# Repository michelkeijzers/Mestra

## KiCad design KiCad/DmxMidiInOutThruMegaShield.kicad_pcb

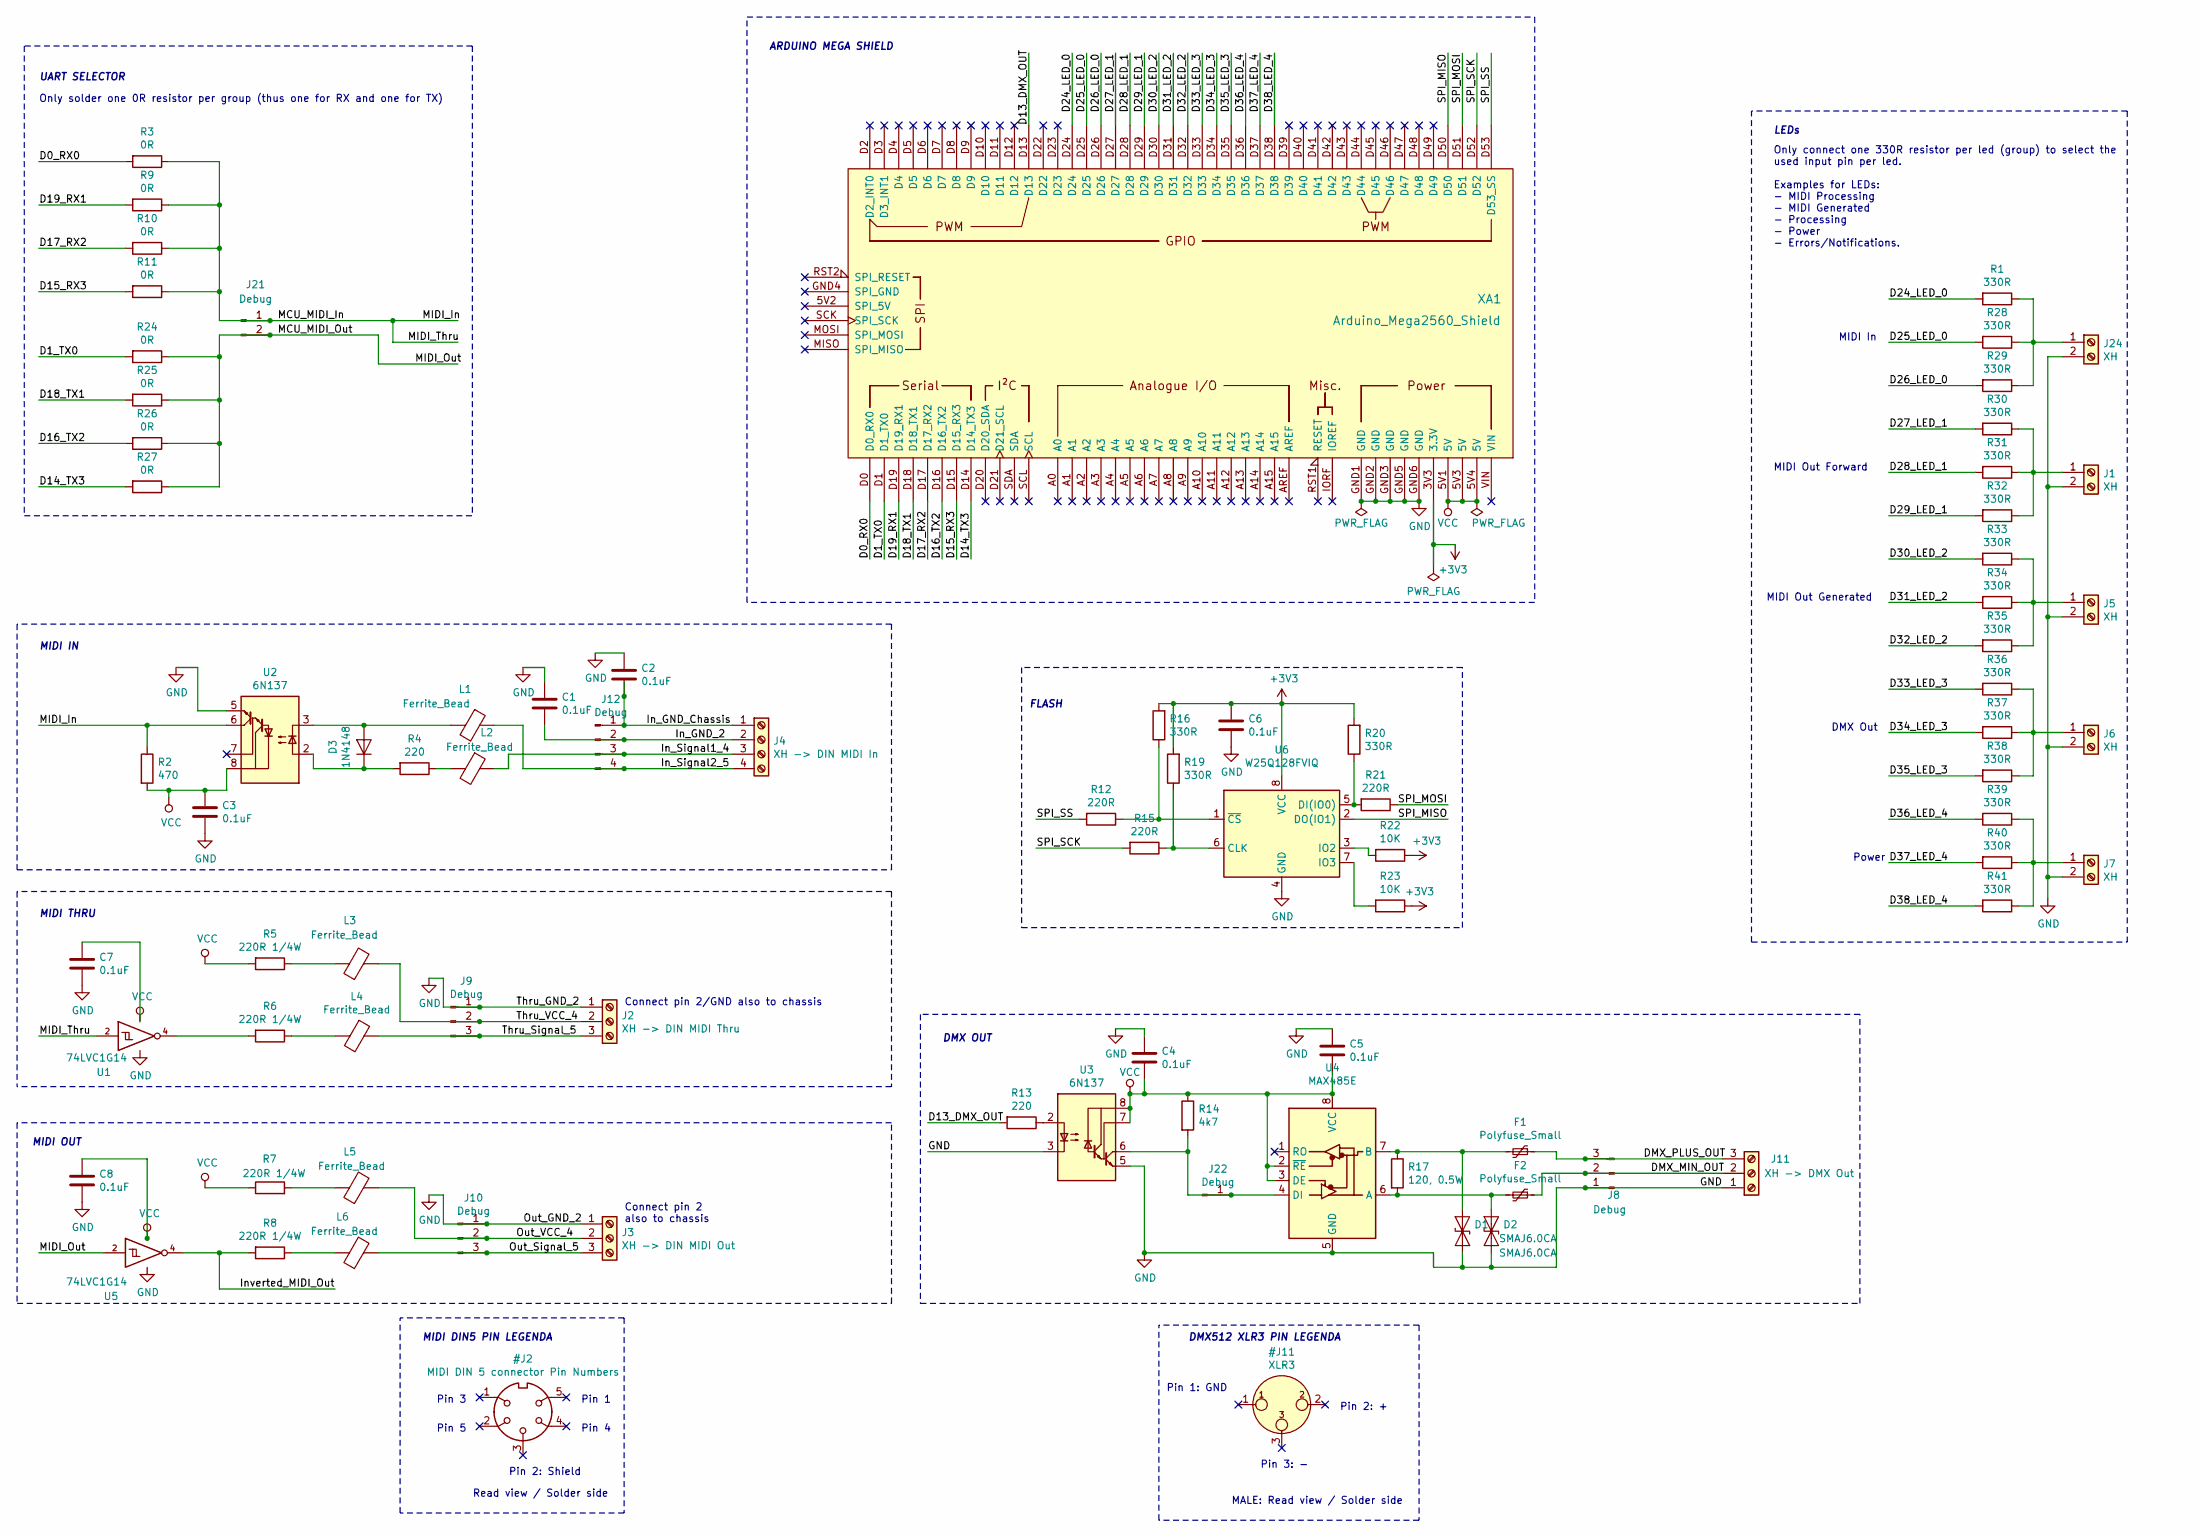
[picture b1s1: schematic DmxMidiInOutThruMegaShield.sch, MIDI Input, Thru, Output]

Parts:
C1, C2, C3, C4, C5, C6, C7, C8: 0.1uF; C_0805_2012Metric_Pad1.15x1.40mm_HandSolder
D1, D2: SMAJ6.0CA; D_SMA_Handsoldering
D3: 1N4148; D_SOD-323_HandSoldering
F1, F2: Polyfuse_Small; Fuse_1812_4532Metric_Pad1.30x3.40mm_HandSolder
J1, J5, J6, J7, J24: XH; JST_XH_S2B-XH-A_1x02_P2.50mm_Horizontal
J2: XH -> DIN MIDI Thru; JST_XH_S3B-XH-A_1x03_P2.50mm_Horizontal
J3: XH -> DIN MIDI Out; JST_XH_S3B-XH-A_1x03_P2.50mm_Horizontal
J4: XH -> DIN MIDI In; JST_XH_S4B-XH-A_1x04_P2.50mm_Horizontal
J8, J9, J10: Debug; PinHeader_1x03_P2.54mm_Vertical
J11: XH -> DMX Out; JST_XH_S3B-XH-A_1x03_P2.50mm_Horizontal
J12: Debug; PinHeader_1x04_P2.54mm_Vertical
J21: Debug; PinHeader_1x02_P2.54mm_Vertical
J22: Debug; PinHeader_1x01_P2.54mm_Vertical
L1, L2, L3, L4, L5, L6: Ferrite_Bead; L_0805_2012Metric_Pad1.15x1.40mm_HandSolder
R1, R16, R19, R20, R28, R29, R30, R31, R32, R33, R34, R35, R36, R37, R38, R39, R40, R41: 330R; R_0805_2012Metric_Pad1.15x1.40mm_HandSolder
R2: 470; R_0805_2012Metric_Pad1.15x1.40mm_HandSolder
R3, R9, R10, R11, R24, R25, R26, R27: 0R; R_0805_2012Metric_Pad1.15x1.40mm_HandSolder
R4, R13: 220; R_0805_2012Metric_Pad1.15x1.40mm_HandSolder
R5, R6, R7, R8: 220R 1/4W; R_0805_2012Metric_Pad1.15x1.40mm_HandSolder
R12, R15, R21: 220R; R_0805_2012Metric_Pad1.15x1.40mm_HandSolder
R14: 4k7; R_0805_2012Metric_Pad1.15x1.40mm_HandSolder
R17: 120, 0.5W; R_0805_2012Metric_Pad1.15x1.40mm_HandSolder
R22, R23: 10K; R_0805_2012Metric_Pad1.15x1.40mm_HandSolder
U1, U5: 74LVC1G14; SOT-23-5_HandSoldering
U2, U3: 6N137; SOP-8_3.76x4.96mm_P1.27mm
U4: MAX485E; SOP-8_3.76x4.96mm_P1.27mm
U6: W25Q128FVIQ; SOIC-8_5.23x5.23mm_P1.27mm
XA1: Arduino_Mega2560_Shield

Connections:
+3V3: C6.1, R16.2, R19.2, R20.2, R22.1, R23.1, U6.8 (VCC), XA1.3V3 (3.3V)
/D0_RX0: R3.2, XA1.D0 (D0_RX0)
/D1_TX0: R24.2, XA1.D1 (D1_TX0)
/D13_DMX_OUT: R13.2, XA1.D13
/D14_TX3: R27.2, XA1.D14 (D14_TX3)
/D15_RX3: R11.2, XA1.D15 (D15_RX3)
/D16_TX2: R26.2, XA1.D16 (D16_TX2)
/D17_RX2: R10.2, XA1.D17 (D17_RX2)
/D18_TX1: R25.2, XA1.D18 (D18_TX1)
/D19_RX1: R9.2, XA1.D19 (D19_RX1)
/D24_LED_0: R1.2, XA1.D24
/D25_LED_0: R28.2, XA1.D25
/D26_LED_0: R29.2, XA1.D26
/D27_LED_1: R30.2, XA1.D27
/D28_LED_1: R31.2, XA1.D28
/D29_LED_1: R32.2, XA1.D29
/D30_LED_2: R33.2, XA1.D30
/D31_LED_2: R34.2, XA1.D31
/D32_LED_2: R35.2, XA1.D32
/D33_LED_3: R36.2, XA1.D33
/D34_LED_3: R37.2, XA1.D34
/D35_LED_3: R38.2, XA1.D35
/D36_LED_4: R39.2, XA1.D36
/D37_LED_4: R40.2, XA1.D37
/D38_LED_4: R41.2, XA1.D38
/DMX_MIN_OUT: F2.1, J8.2, J11.2
/DMX_PLUS_OUT: F1.1, J8.3, J11.3
/In_GND_2: C1.2, J4.2, J12.2
/In_GND_Chassis: C2.2, J4.1, J12.1
/In_Signal1_4: J4.3, J12.3, L2.1
/In_Signal2_5: J4.4, J12.4, L1.1
/Inverted_MIDI_Out: R8.2, U5.4
/MCU_MIDI_In: J21.1, R2.1, R3.1, R9.1, R10.1, R11.1, U1.2, U2.6 (VO2)
/MCU_MIDI_Out: J21.2, R24.1, R25.1, R26.1, R27.1, U5.2
/Out_Signal_5: J3.3, J10.3, L6.2
/Out_VCC_4: J3.2, J10.2, L5.2
/SPI_MISO: U6.2 (DO(IO1)), XA1.D50
/SPI_MOSI: R21.1, XA1.D51
/SPI_SCK: R15.2, XA1.D52
/SPI_SS: R12.2, XA1.D53 (D53_SS)
/Thru_Signal_5: J2.3, J9.3, L4.1
/Thru_VCC_4: J2.2, J9.2, L3.2
GND: C1.1, C2.1, C3.2, C4.1, C5.1, C6.2, C7.2, C8.2, D1.1 (A1), D2.1 (A1), J1.2, J2.1, J3.1, J5.2, J6.2, J7.2, J8.1, J9.1, J10.1, J11.1, J24.2, U1.3 (GND), U2.5 (GND), U3.3 (C2), U3.5 (GND), U4.5 (GND), U5.3 (GND), U6.4 (GND), XA1.GND1 (GND), XA1.GND2 (GND), XA1.GND3 (GND), XA1.GND5 (GND), XA1.GND6 (GND)
unnamed: D1.2 (A2), F1.2, R17.1, U4.7 (B)
unnamed: D2.2 (A2), F2.2, R17.2, U4.6 (A)
unnamed: D3.1 (K), R4.2, U2.2 (C1)
unnamed: D3.2 (A), L1.2, U2.3 (C2)
unnamed: J1.1, R30.1, R31.1, R32.1
unnamed: J5.1, R33.1, R34.1, R35.1
unnamed: J6.1, R36.1, R37.1, R38.1
unnamed: J7.1, R39.1, R40.1, R41.1
unnamed: J22.1, R14.2, U3.6 (VO2), U4.4 (DI)
unnamed: J24.1, R1.1, R28.1, R29.1
unnamed: L2.2, R4.1
unnamed: L3.1, R5.1
unnamed: L4.2, R6.1
unnamed: L5.1, R7.2
unnamed: L6.1, R8.1
unnamed: R6.2, U1.4
unnamed: R12.1, R16.1, U6.1 (~CS)
unnamed: R13.1, U3.2 (C1)
unnamed: R15.1, R19.1, U6.6 (CLK)
unnamed: R20.1, R21.2, U6.5 (DI(IO0))
unnamed: R22.2, U6.3 (IO2)
unnamed: R23.2, U6.7 (IO3)
VCC: C3.1, C4.2, C5.2, C7.1, C8.1, R2.2, R5.2, R7.1, R14.1, U1.5 (VCC), U2.8 (VCC), U3.7 (VO1), U3.8 (VCC), U4.2 (~RE), U4.3 (DE), U4.8 (VCC), U5.5 (VCC), XA1.5V1 (5V), XA1.5V3 (5V), XA1.5V4 (5V)

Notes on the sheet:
Read view / Solder side
Pin 1
Pin 4
Pin 2: Shield
Pin 5
Pin 3
MIDI DIN5 PIN LEGENDA
MALE: Read view / Solder side
Pin 2: +
Pin 3: -
Pin 1: GND
DMX512 XLR3 PIN LEGENDA
DMX OUT
Connect pin 2/GND also to chassis
MIDI THRU
Connect pin 2 also to chassis
MIDI OUT
LEDs
ARDUINO MEGA SHIELD
MIDI In
MIDI Out Forward
MIDI Out Generated
Power
FLASH
DMX Out
Only connect one 330R resistor per led (group) to select the used input pin per led. Examples for LEDs: - MIDI Processing - MIDI Generated - Processing - Power - Errors/Notifications.
Only solder one 0R resistor per group (thus one for RX and one for TX)
UART SELECTOR
MIDI IN

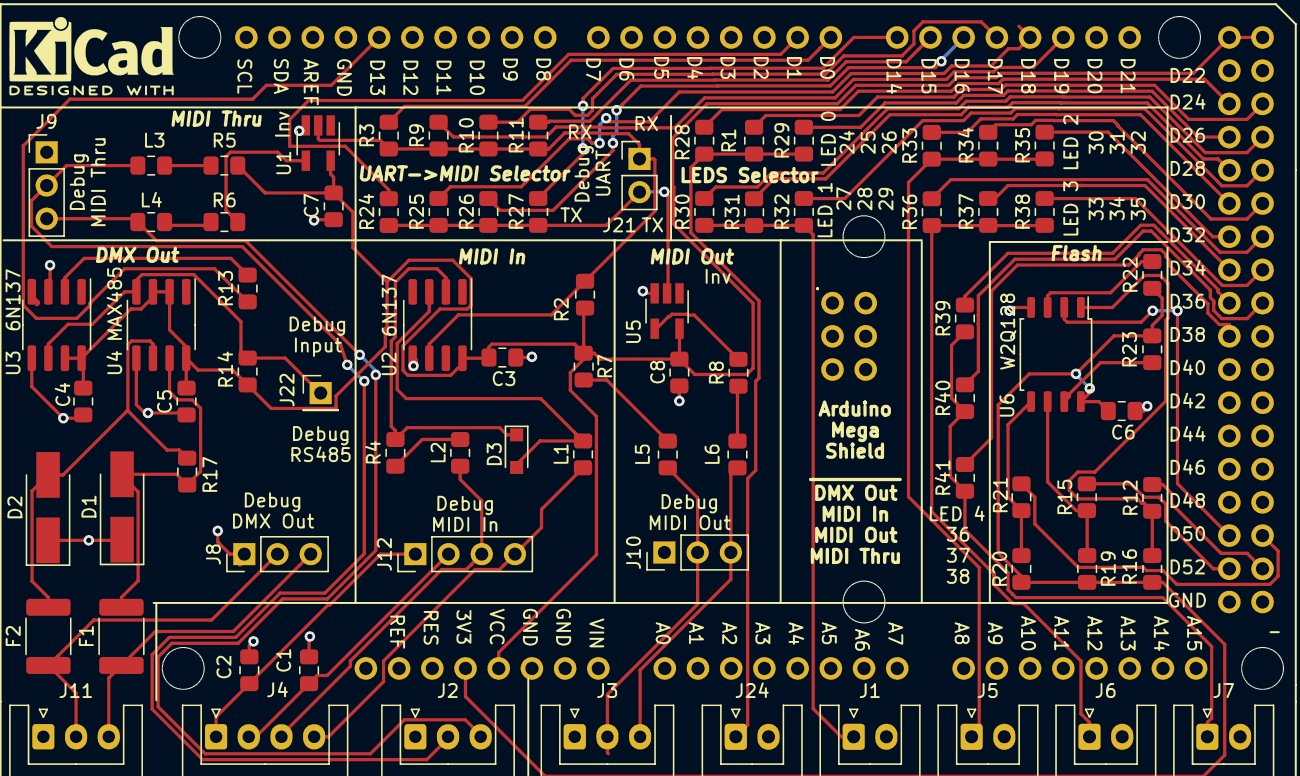
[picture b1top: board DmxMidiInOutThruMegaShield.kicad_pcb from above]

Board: 2 copper layers, 81 parts (0 on the bottom side), 66 nets.

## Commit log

2017-11-08 Sheets/tables
    for mestra
2017-11-08 Add files via upload
    Adding some split documentation files
2017-11-08 Added general requirements and updated design decisions
2017-11-10 Auto stash before merge of "master" and "origin/master"
    Added communication document
2017-11-16 Add info to add (in excell)
2017-11-17 Auto stash before merge of "master" and "origin/master"
    Split Devices/controller only, added communication between devices and more.
2017-11-17 Function MIDI List
2017-11-20 Triggers/Instructions / folders
2017-11-20 Audio slave
2017-11-20 More slaves
2017-11-22 Sheet excel triggers
2017-11-24 Workflow
2017-11-27 Split slaves
2017-11-28 Auto stash before merge of "master" and "origin/master"
    Triggers/instructions
2017-11-29 Created triggers, instructions and workflow adaptations
2017-11-29 Added remote + dmx info in appendixi to add
2017-12-01 Dmx added instructions
2017-12-03 Abbrev
2017-12-03 Setup
2017-12-06 Syntax
2017-12-13 Small changes in triggers
2017-12-20 DMX To Add
2017-12-21 DMX Instructions
2017-12-22 Triggers
2017-12-24 Auto stash before merge of "master" and "origin/master"
    Triggers
2018-01-16 Unclear
2018-01-17 Code
2018-01-23 Revert "Merge remote-tracking branch 'origin/master'"
    This reverts commit 67b7317925701db91b79f478d1c8e19bb5d96f62.
2018-01-23 Auto stash before merge of "master" and "origin/master"
    Doc changes, variables added
2019-05-17 Add project files.
2019-05-17 Add .gitignore and .gitattributes.
2019-05-19 Fade/Chase + Strobo done (not fully checked), next: LED Bar
2019-05-20 Created virtual classes for Par/Fixtures, Next: LightSetup
2019-05-20 Test files changed to Mcu/Win versions using strategy pattern.
2019-05-20 Fixed Ino for initializing LightSetup + rearranged Windows.cpp
2019-05-22 Windows LED Par GUI, separate LEDs
2019-05-23 Fixed various problems (added McuLightSetup to Ino file, fixed bug in program 62, created debug flags for color checking/screen updating, ...)
2019-05-25 Finished rainbow colors
2019-05-26 Partly Chinese Par/LED bar segment split.
2019-05-28 LED Bar works. TODO: color of ledbar too dark
2019-06-01 SRAM works
2019-06-02 Multiple ASCII commands, various compiler error warnings (Unsigned/signed)
2019-06-02 Fixed (kind of) assert, see stack exchange question, removed more warnings, fixed reading of parameters.
2019-06-02 Fixed ledbar DMX channel problem.
2019-06-03 Renamed #defines (added name of class, set 3 segment mode for Led bars.
2019-07-09 Added activate trigger, fixed warnings
2019-07-10 Fixed trigger programs, also fixed problem in performance issue because for all parbits, all pars where set when a program is set; now only the current par is set.
2019-07-11 Minimized ino, minimized C++/standard/cstd library usage.
2019-07-11 Added trigger state to output table, added refresh rate on screen
2019-07-14 Added packed command, added c(command option) for commands, fixed problems in programs 50 and 70, added hold/once and trigger functionality.
2019-07-14 Added most simple version of Arduino stubs.
2019-07-18 Extended Arduino stubs.
2019-07-20 Added time table, step time enum, color enum, changes to pack/unpack functions. Added commands class. NOTE: pack/unpack was not used before, and is broken currently.
2019-07-22 Xtext grammar, Song class, additional bits utils
2019-07-22 Changed location of test mestradmx
2019-07-24 Extended grammar, has some problems, but is complete. Instance needs to be filled in with more useful lines.
2019-07-25 Added MDE classpath, fixed grammar (now complete and working), added test grammar instance (parses ok). TODO: Xpand code.
2019-08-04 Added DMX validations, to add: MIDI validations; adapted grammar that all sequences/steps/triggers/commands/rules are on highest level, parser has to be adapted.
2019-08-12 Changed grammar
2019-08-12 Kicad
